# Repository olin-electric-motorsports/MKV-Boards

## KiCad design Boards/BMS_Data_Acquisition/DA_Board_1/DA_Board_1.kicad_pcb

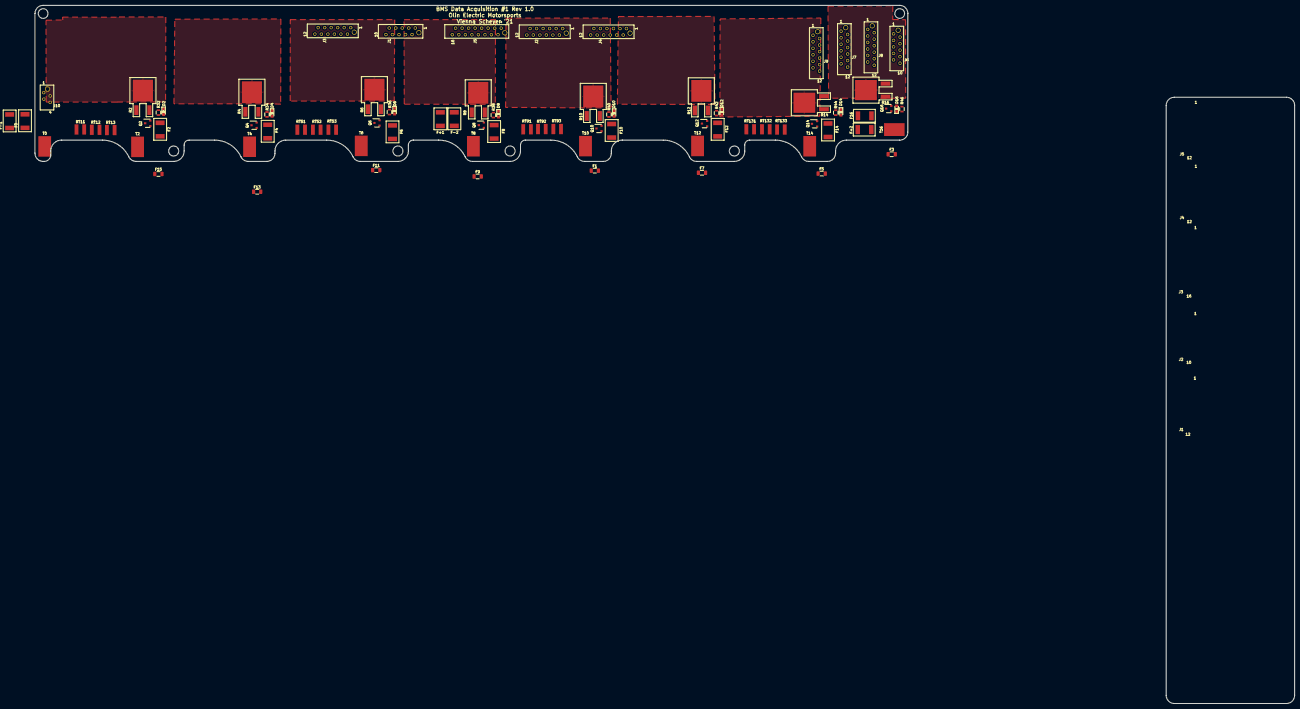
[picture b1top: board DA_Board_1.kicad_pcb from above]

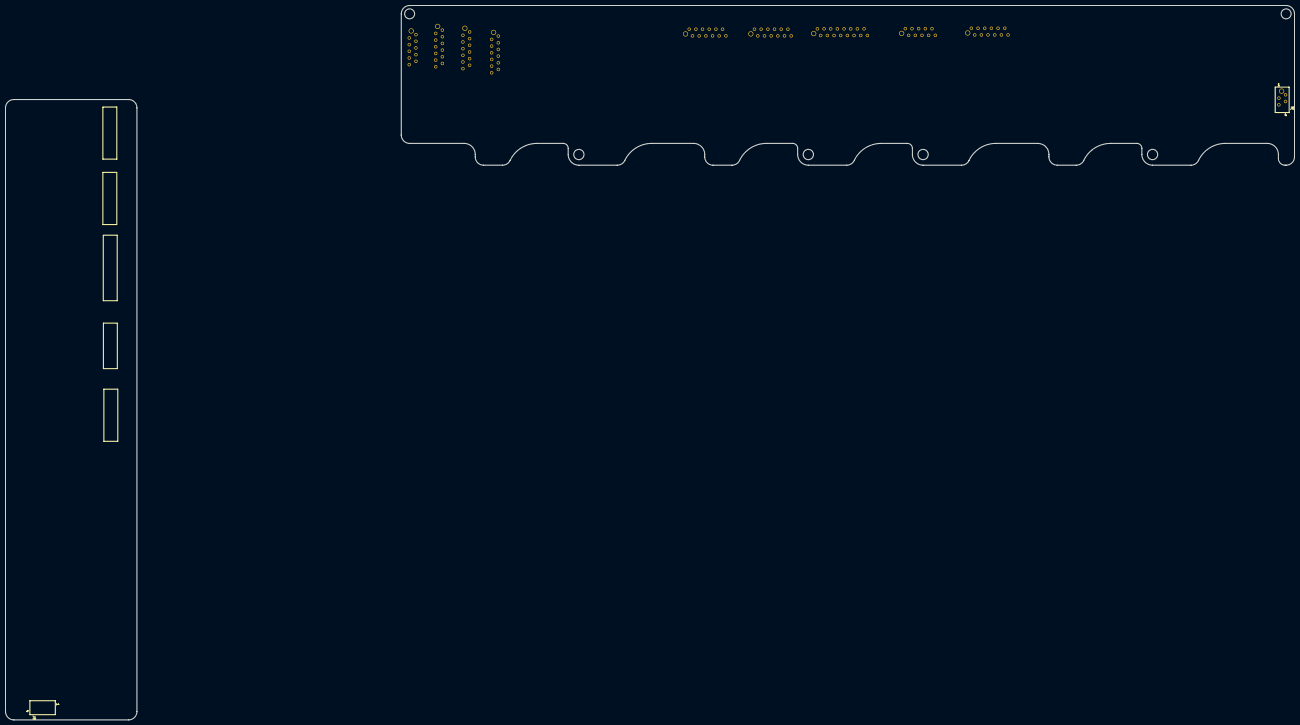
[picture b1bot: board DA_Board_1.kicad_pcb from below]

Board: 2 copper layers, 340.1 x 60.8 mm, 91 parts (7 on the bottom side), 103 nets, no tracks yet.

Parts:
D2, D4, D6, D8, D10, D12, D14, D16: LED_0805; LED_0805_OEM
F0, F2, F4, F6, F8, F10, F12, F14, F16: 200mA_Fuse; Fuse_1812
F1, F3, F5, F7, F9, F11, F13, F15: 1.5A_Fuse; Fuse_1206
F+1, F+2: 200mA_Fuse; Fuse_1812
F-1, F-2: 200mA_Fuse; Fuse_1812
J1, J4: MM_F_VT_12; micromatch_female_vt_12
J1#2, J6: MM_M_VT_10; micromatch_female_vert_10
J2: MM_F_VT_10; micromatch_female_vert_10
J2#2, J3#2, J4#2, J7, J8#3, J9: MM_M_VT_12; micromatch_female_vert_12
J3: MM_F_VT_16; micromatch_female_vert_16
J5: MM_M_VT_12; micromatch_female_vt_12
J5#2: MM_M_VT_16; micromatch_female_vert_16
J8, J8#2, J10: MM_F_VT_04; micromatch_female_vert_4
Q2, Q4, Q6, Q8, Q10, Q12, Q14, Q16: BSS308PE; SOT-23-3_OEM
R2, R4, R6, R8, R10, R12, R14, R16: R_3.3_25W_TO163; PWR163
R32, R34, R36, R38, R40, R42, R44, R46: R_475; R_0805_OEM
RT11, RT12, RT13, RT51, RT52, RT53, RT91, RT92, RT93, RT131, RT132, RT133: Thermistor
T0, T2, T4, T6, T8, T10, T12, T14, T16: Tab_Connect_BMS; Tab_connect_BMS

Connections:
/C0: F0.2, J1#2.9
/C1: J1#2.8, J9.1
/C1_T1: J1#2.7, RT11.1
/C1_T2: J1#2.6, RT12.1
/C1_T3: J1#2.5, RT13.1
/C2: F2.2, J2#2.11
/C3: J1#2.4, J9.8
/C3_T1: J2#2.9, J9.7
/C3_T2: J2#2.8, J9.6
/C3_T3: J2#2.7, J9.5
/C4: F4.2, J2#2.10
/C5: J1#2.3, J9.12
/C5_T1: J1#2.2, RT51.1
/C5_T2: J1#2.1, RT52.1
/C5_T3: J3#2.12, RT53.1
/C6: F6.2, J2#2.6
/C7: J3#2.11, J7.8
/C7_T1: J2#2.2, J7.7
/C7_T2: J2#2.1, J7.6
/C7_T3: J4#2.12, J7.5
/C8: F8.2, J2#2.3
/C9: J3#2.10, J7.12
/C9_T1: J3#2.9, RT91.1
/C9_T2: J3#2.8, RT92.1
/C9_T3: J3#2.7, RT93.1
/C10: F10.2, J4#2.11
/C11: J3#2.6, J8#3.7
/C11_T1: J4#2.9, J8#3.6
/C11_T2: J4#2.8, J8#3.5
/C11_T3: J4#2.7, J8#3.4
/C12: F12.2, J4#2.10
/C13: J3#2.5, J8#3.11
/C13_T1: J3#2.4, RT131.1
/C13_T2: J3#2.3, RT132.1
/C13_T3: J3#2.2, RT133.1
/C14: F14.2, J4#2.6
/C15: J3#2.1, J6.8
/C15_T1: J4#2.3, J6.5
/C15_T2: J4#2.2, J6.4
/C15_T3: J4#2.1, J6.3
/C16: F16.2, J4#2.4
/GND1: J2#2.12, J6.6, RT11.2, RT12.2, RT13.2, RT51.2, RT52.2, RT53.2, RT91.2, RT92.2, RT93.2, RT131.2, RT132.2, RT133.2
/PWR1: F0.1, F-1.1, J9.2, T0.1
/PWR2: J9.4, R2.2, R32.2
/PWR3: F2.1, F15.1, J9.9, T2.1
/PWR4: J9.11, R4.2, R34.2
/PWR5: F4.1, F13.1, J7.2, T4.1
/PWR6: J7.4, R6.2, R36.2
/PWR7: F6.1, F11.1, J7.9, T6.1
/PWR8: J7.11, R8.2, R38.2
/PWR9: F8.1, F9.1, F+1.1, F-2.1, J8#3.1, T8.1
/PWR10: J8#3.3, R10.2, R40.2
/PWR11: F1.1, F10.1, J8#3.8, T10.1
/PWR12: J8#3.10, R12.2, R42.2
/PWR13: F7.1, F12.1, J8#3.12, T12.1
/PWR14: J6.2, R14.2, R44.2
/PWR15: F5.1, F14.1, J6.10, T14.1
/PWR16: J6.7, R16.2, R46.2
/Q1: J5#2.16, J9.3
/Q2: J5#2.15, Q2.1
/Q3: J5#2.14, J9.10
/Q4: J5#2.13, Q4.1
/Q5: J5#2.12, J7.3
/Q6: J5#2.11, Q6.1
/Q7: J5#2.10, J7.10
/Q8: J5#2.9, Q8.1
/Q9: J5#2.8, J8#3.2
/Q10: J5#2.7, Q10.1
/Q11: J5#2.6, J8#3.9
/Q12: J5#2.5, Q12.1
/Q13: J5#2.4, J6.1
/Q14: J5#2.3, Q14.1
/Q15: J5#2.2, J6.9
/Q16: J5#2.1, Q16.1
/V+1: F+1.2, J4#2.5
/V+2: F+2.2, J2#2.5
/V-1: F-1.2, J2#2.4
/V-2: F-2.2, J1#2.10
unnamed: D2.1, R32.1
unnamed: D2.2, Q2.3, R2.1
unnamed: D4.1, R34.1
unnamed: D4.2, Q4.3, R4.1
unnamed: D6.1, R36.1
unnamed: D6.2, Q6.3, R6.1
unnamed: D8.1, R38.1
unnamed: D8.2, Q8.3, R8.1
unnamed: D10.1, R40.1
unnamed: D10.2, Q10.3, R10.1
unnamed: D12.1, R42.1
unnamed: D12.2, Q12.3, R12.1
unnamed: D14.1, R44.1
unnamed: D14.2, Q14.3, R14.1
unnamed: D16.1, R46.1
unnamed: D16.2, Q16.3, R16.1
unnamed: F1.2, Q10.2
unnamed: F3.2, Q16.2
unnamed: F5.2, Q14.2
unnamed: F7.2, Q12.2
unnamed: F9.2, Q8.2
unnamed: F11.2, Q6.2
unnamed: F13.2, Q4.2
unnamed: F15.2, Q2.2
unnamed: F3.1, F16.1, F+2.1, T16.1

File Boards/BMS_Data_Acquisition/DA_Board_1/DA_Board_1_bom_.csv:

Component,Description,Part,References,Value,Footprint,Quantity Per PCB,Datasheet,MPN,MFN,PurchasingLink
1,"LED, Green, 2.2V, 20mA, 0805",LED_0805,D2 D4 D6 D8 D10 D12 D14 D16,LED_0805,LED_0805_OEM,8,http://www.osram-os.com/Graphics/XPic9/00078860_0.pdf,475-1410-1-ND,DK,https://www.digikey.com/products/en?keywords=475-1410-1-ND
2,200mA Fuse,200mA_Fuse,F0 F2 F4 F6 F8 F10 F12 F14 F16 F+1 F+2 F-1 F-2,200mA_Fuse,Fuse_1812,13,https://www.belfuse.com/resources/CircuitProtection/datashee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,,,
3,Micro-MaTch connector 10 pin male vertical,MM_M_VT_10,J1 J6,MM_M_VT_10,micromatch_female_vert_10,2,http://www.te.com/commerce/DocumentDelivery/DDEController?Ac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,1-215464-0,TE,http://www.te.com/global-en/product-1-215464-0.html
4,Micro-MaTch connector 12 pin male vertical,MM_M_VT_12,J2 J3 J4 J7 J8 J9,MM_M_VT_12,micromatch_female_vert_12,6,http://www.te.com/commerce/DocumentDelivery/DDEController?Ac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,1-215464-2,TE,http://www.te.com/global-en/product-1-215464-2.html
5,Micro-MaTch connector 16 pin male vertical,MM_M_VT_16,J5,MM_M_VT_16,micromatch_female_vert_16,1,http://www.te.com/commerce/DocumentDelivery/DDEController?Ac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,1-215464-6,TE,http://www.te.com/global-en/product-1-215464-6.html
6,"MOSFET, P-channel, 30V, 2A",BSS308PE,Q2 Q4 Q6 Q8 Q10 Q12 Q14 Q16,BSS308PE,SOT-23-3_OEM,8,https://www.infineon.com/dgdl/BSS308PE_Rev2.03.pdf?folderId=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,BSS308PEH6327XTSA1CT-ND,DK,https://www.digikey.com/products/en/discrete-semiconductor-p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
7,RES SMD 3.3 OHM 1% 25W DPAK,R_3.3_25W_TO163,R2 R4 R6 R8 R10 R12 R14 R16,R_3.3_25W_TO163,PWR163,8,https://www.bourns.com/docs/Product-Datasheets/PWR163.pdf,PWR163S-25-3R30F-ND,DK,https://www.digikey.com/products/en?keywords=PWR163S-25-3R30F-ND
8,"Resistor, 475, 0.125W, 1%, 0805",R_475,R32 R34 R36 R38 R40 R42 R44 R46,R_475,R_0805_OEM,8,http://www.yageo.com.tw/exep/pages/download/literatures/PYu-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,311-475CRCT-ND,DK,https://www.digikey.com/products/en?keywords=311-475CRCT-ND
9,,Thermistor,RT11 RT12 RT13 RT51 RT52 RT53 RT91 RT92 RT93 RT131 RT132 RT133,Thermistor,Thermistor,12,,,,
10,,Tab_Connect_BMS,T0 T2 T4 T6 T8 T10 T12 T14 T16,Tab_Connect_BMS,Tab_connect_BMS,9,,,,
,,,,,,,,,,
,,,,,,,,,,
,,,,,,,,,,
,,,,,,,,,,
,,,,,,,,,,
Component Groups:,10,,,,,,,,,
Component Count:,75,,,,,,,,,
Fitted Components:,75,,,,,,,,,
Number of PCBs:,1,,,,,,,,,
Total components:,75,,,,,,,,,
Schematic Version:,,,,,,,,,,
Schematic Date:,2019-09-18,,,,,,,,,
PCB Variant:,[u'default'],,,,,,,,,
BoM Date:,Mon 11 Nov 2019 08:43:34 PM EST,,,,,,,,,
Schematic Source:,/home/vscheyer/Desktop/Formula/MKV-Boards/Boards/BMS_Data_Acquisition/DA_Board_1/DA_Board_1.sch,,,,,,,,,
KiCad Version:,Eeschema 5.0.2-bee76a0~70~ubuntu16.04.1,,,,,,,,,

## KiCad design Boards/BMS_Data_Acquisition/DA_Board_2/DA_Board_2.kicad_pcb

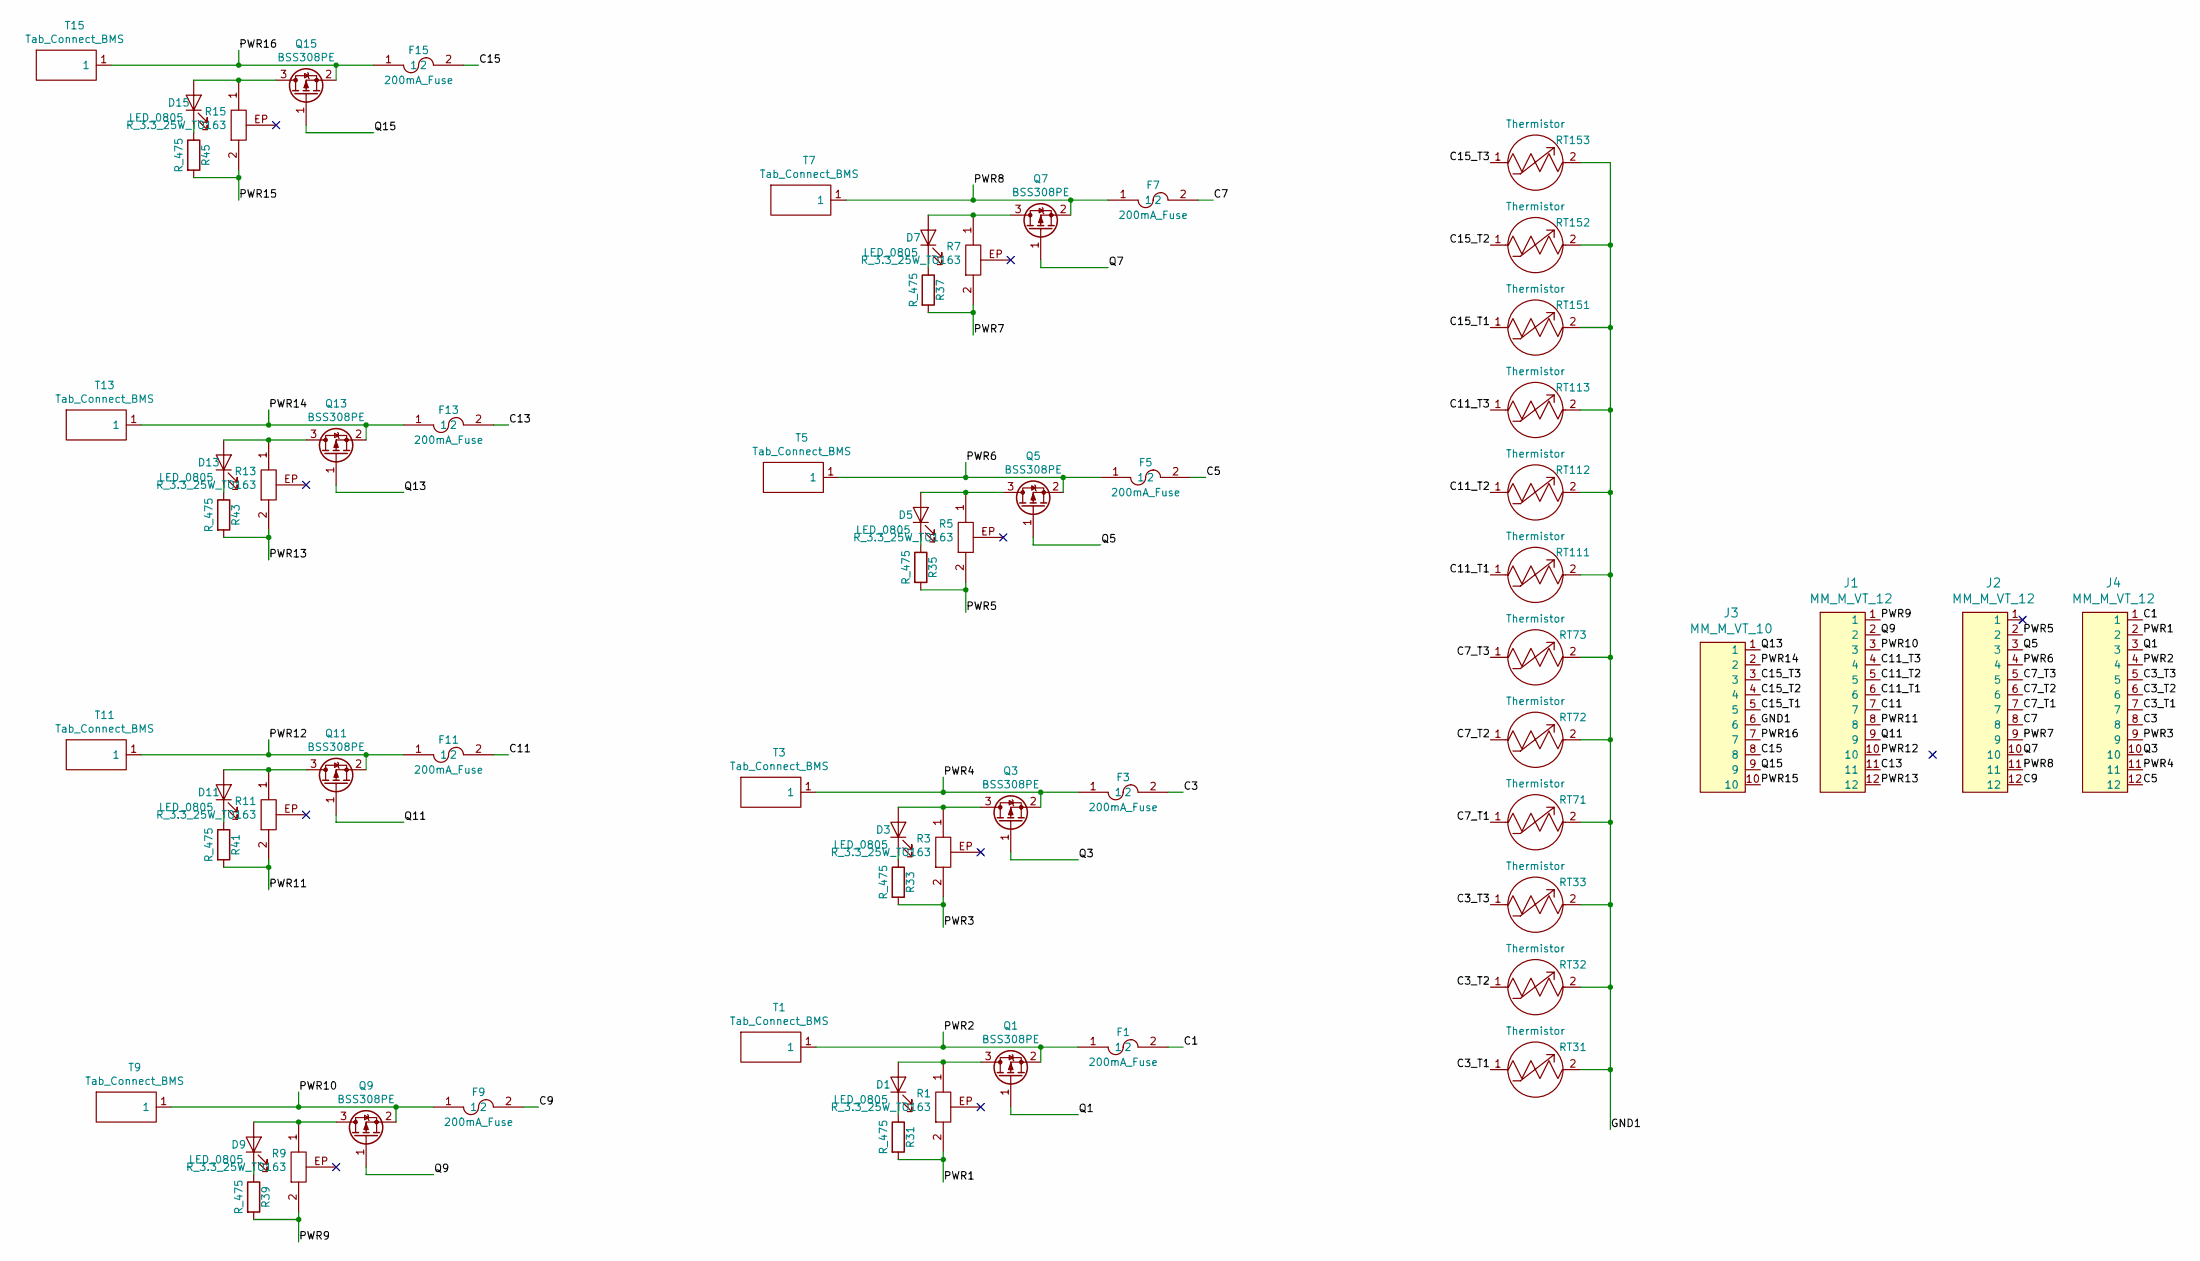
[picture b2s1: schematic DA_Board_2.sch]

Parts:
D1, D3, D5, D7, D9, D11, D13, D15: LED_0805; LED_0805_OEM; MPN 475-1410-1-ND
F1, F3, F5, F7, F9, F11, F13, F15: 200mA_Fuse; Fuse_1812
J1, J2, J4: MM_M_VT_12; micromatch_female_vert_12; MPN 1-215464-2
J3: MM_M_VT_10; micromatch_female_vert_10; MPN 1-215464-0
Q1, Q3, Q5, Q7, Q9, Q11, Q13, Q15: BSS308PE; SOT-23-3_OEM; MPN BSS308PEH6327XTSA1CT-ND
R1, R3, R5, R7, R9, R11, R13, R15: R_3.3_25W_TO163; PWR163; MPN PWR163S-25-3R30F-ND
R31, R33, R35, R37, R39, R41, R43, R45: R_475; R_0805_OEM; MPN 311-475CRCT-ND
RT31, RT32, RT33, RT71, RT72, RT73, RT111, RT112, RT113, RT151, RT152, RT153: Thermistor
T1, T3, T5, T7, T9, T11, T13, T15: Tab_Connect_BMS; Tab_connect_BMS

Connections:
/C1: F1.2, J4.1
/C3: F3.2, J4.8
/C3_T1: J4.7, RT31.1
/C3_T2: J4.6, RT32.1
/C3_T3: J4.5, RT33.1
/C5: F5.2, J4.12
/C7: F7.2, J2.8
/C7_T1: J2.7, RT71.1
/C7_T2: J2.6, RT72.1
/C7_T3: J2.5, RT73.1
/C9: F9.2, J2.12
/C11: F11.2, J1.7
/C11_T1: J1.6, RT111.1
/C11_T2: J1.5, RT112.1
/C11_T3: J1.4, RT113.1
/C13: F13.2, J1.11
/C15: F15.2, J3.8
/C15_T1: J3.5, RT151.1
/C15_T2: J3.4, RT152.1
/C15_T3: J3.3, RT153.1
/GND1: J3.6, RT31.2, RT32.2, RT33.2, RT71.2, RT72.2, RT73.2, RT111.2, RT112.2, RT113.2, RT151.2, RT152.2, RT153.2
/PWR1: J4.2, R1.2, R31.2
/PWR2: F1.1, J4.4, Q1.2 (S), T1.1
/PWR3: J4.9, R3.2, R33.2
/PWR4: F3.1, J4.11, Q3.2 (S), T3.1
/PWR5: J2.2, R5.2, R35.2
/PWR6: F5.1, J2.4, Q5.2 (S), T5.1
/PWR7: J2.9, R7.2, R37.2
/PWR8: F7.1, J2.11, Q7.2 (S), T7.1
/PWR9: J1.1, R9.2, R39.2
/PWR10: F9.1, J1.3, Q9.2 (S), T9.1
/PWR11: J1.8, R11.2, R41.2
/PWR12: F11.1, J1.10, Q11.2 (S), T11.1
/PWR13: J1.12, R13.2, R43.2
/PWR14: F13.1, J3.2, Q13.2 (S), T13.1
/PWR15: J3.10, R15.2, R45.2
/PWR16: F15.1, J3.7, Q15.2 (S), T15.1
/Q1: J4.3, Q1.1 (G)
/Q3: J4.10, Q3.1 (G)
/Q5: J2.3, Q5.1 (G)
/Q7: J2.10, Q7.1 (G)
/Q9: J1.2, Q9.1 (G)
/Q11: J1.9, Q11.1 (G)
/Q13: J3.1, Q13.1 (G)
/Q15: J3.9, Q15.1 (G)
unnamed: D1.1 (K), R31.1
unnamed: D1.2 (A), Q1.3 (D), R1.1
unnamed: D3.1 (K), R33.1
unnamed: D3.2 (A), Q3.3 (D), R3.1
unnamed: D5.1 (K), R35.1
unnamed: D5.2 (A), Q5.3 (D), R5.1
unnamed: D7.1 (K), R37.1
unnamed: D7.2 (A), Q7.3 (D), R7.1
unnamed: D9.1 (K), R39.1
unnamed: D9.2 (A), Q9.3 (D), R9.1
unnamed: D11.1 (K), R41.1
unnamed: D11.2 (A), Q11.3 (D), R11.1
unnamed: D13.1 (K), R43.1
unnamed: D13.2 (A), Q13.3 (D), R13.1
unnamed: D15.1 (K), R45.1
unnamed: D15.2 (A), Q15.3 (D), R15.1

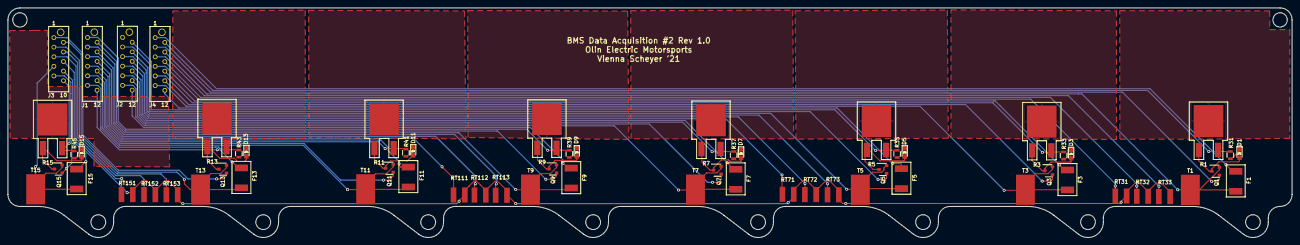
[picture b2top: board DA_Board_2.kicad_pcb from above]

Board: 2 copper layers, 340.1 x 60.8 mm, 64 parts (0 on the bottom side), 61 nets.

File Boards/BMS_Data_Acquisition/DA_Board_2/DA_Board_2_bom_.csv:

Component,Description,Part,References,Value,Footprint,Quantity Per PCB,Datasheet,MPN,MFN,PurchasingLink
1,"LED, Green, 2.2V, 20mA, 0805",LED_0805,D1 D3 D5 D7 D9 D11 D13 D15,LED_0805,LED_0805_OEM,8,http://www.osram-os.com/Graphics/XPic9/00078860_0.pdf,475-1410-1-ND,DK,https://www.digikey.com/products/en?keywords=475-1410-1-ND
2,200mA Fuse,200mA_Fuse,F1 F3 F5 F7 F9 F11 F13 F15,200mA_Fuse,Fuse_1812,8,https://www.belfuse.com/resources/CircuitProtection/datashee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,,,
3,Micro-MaTch connector 10 pin male vertical,MM_M_VT_10,J3,MM_M_VT_10,micromatch_female_vert_10,1,http://www.te.com/commerce/DocumentDelivery/DDEController?Ac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,1-215464-0,TE,http://www.te.com/global-en/product-1-215464-0.html
4,Micro-MaTch connector 12 pin male vertical,MM_M_VT_12,J1 J2 J4,MM_M_VT_12,micromatch_female_vert_12,3,http://www.te.com/commerce/DocumentDelivery/DDEController?Ac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,1-215464-2,TE,http://www.te.com/global-en/product-1-215464-2.html
5,"MOSFET, P-channel, 30V, 2A",BSS308PE,Q1 Q3 Q5 Q7 Q9 Q11 Q13 Q15,BSS308PE,SOT-23-3_OEM,8,https://www.infineon.com/dgdl/BSS308PE_Rev2.03.pdf?folderId=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,BSS308PEH6327XTSA1CT-ND,DK,https://www.digikey.com/products/en/discrete-semiconductor-p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
6,RES SMD 3.3 OHM 1% 25W DPAK,R_3.3_25W_TO163,R1 R3 R5 R7 R9 R11 R13 R15,R_3.3_25W_TO163,PWR163,8,https://www.bourns.com/docs/Product-Datasheets/PWR163.pdf,PWR163S-25-3R30F-ND,DK,https://www.digikey.com/products/en?keywords=PWR163S-25-3R30F-ND
7,"Resistor, 475, 0.125W, 1%, 0805",R_475,R31 R33 R35 R37 R39 R41 R43 R45,R_475,R_0805_OEM,8,http://www.yageo.com.tw/exep/pages/download/literatures/PYu-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,311-475CRCT-ND,DK,https://www.digikey.com/products/en?keywords=311-475CRCT-ND
8,,Thermistor,RT31 RT32 RT33 RT71 RT72 RT73 RT111 RT112 RT113 RT151 RT152 RT153,Thermistor,Thermistor,12,,,,
9,,Tab_Connect_BMS,T1 T3 T5 T7 T9 T11 T13 T15,Tab_Connect_BMS,Tab_connect_BMS,8,,,,
,,,,,,,,,,
,,,,,,,,,,
,,,,,,,,,,
,,,,,,,,,,
,,,,,,,,,,
Component Groups:,9,,,,,,,,,
Component Count:,64,,,,,,,,,
Fitted Components:,64,,,,,,,,,
Number of PCBs:,1,,,,,,,,,
Total components:,64,,,,,,,,,
Schematic Version:,,,,,,,,,,
Schematic Date:,,,,,,,,,,
PCB Variant:,default,,,,,,,,,
BoM Date:,Mon 11 Nov 2019 08:40:20 PM EST,,,,,,,,,
Schematic Source:,/home/vscheyer/Desktop/Formula/MKV-Boards/Boards/BMS_Data_Acquisition/DA_Board_2/DA_Board_2.sch,,,,,,,,,
KiCad Version:,Eeschema 5.0.2-bee76a0~70~ubuntu16.04.1,,,,,,,,,

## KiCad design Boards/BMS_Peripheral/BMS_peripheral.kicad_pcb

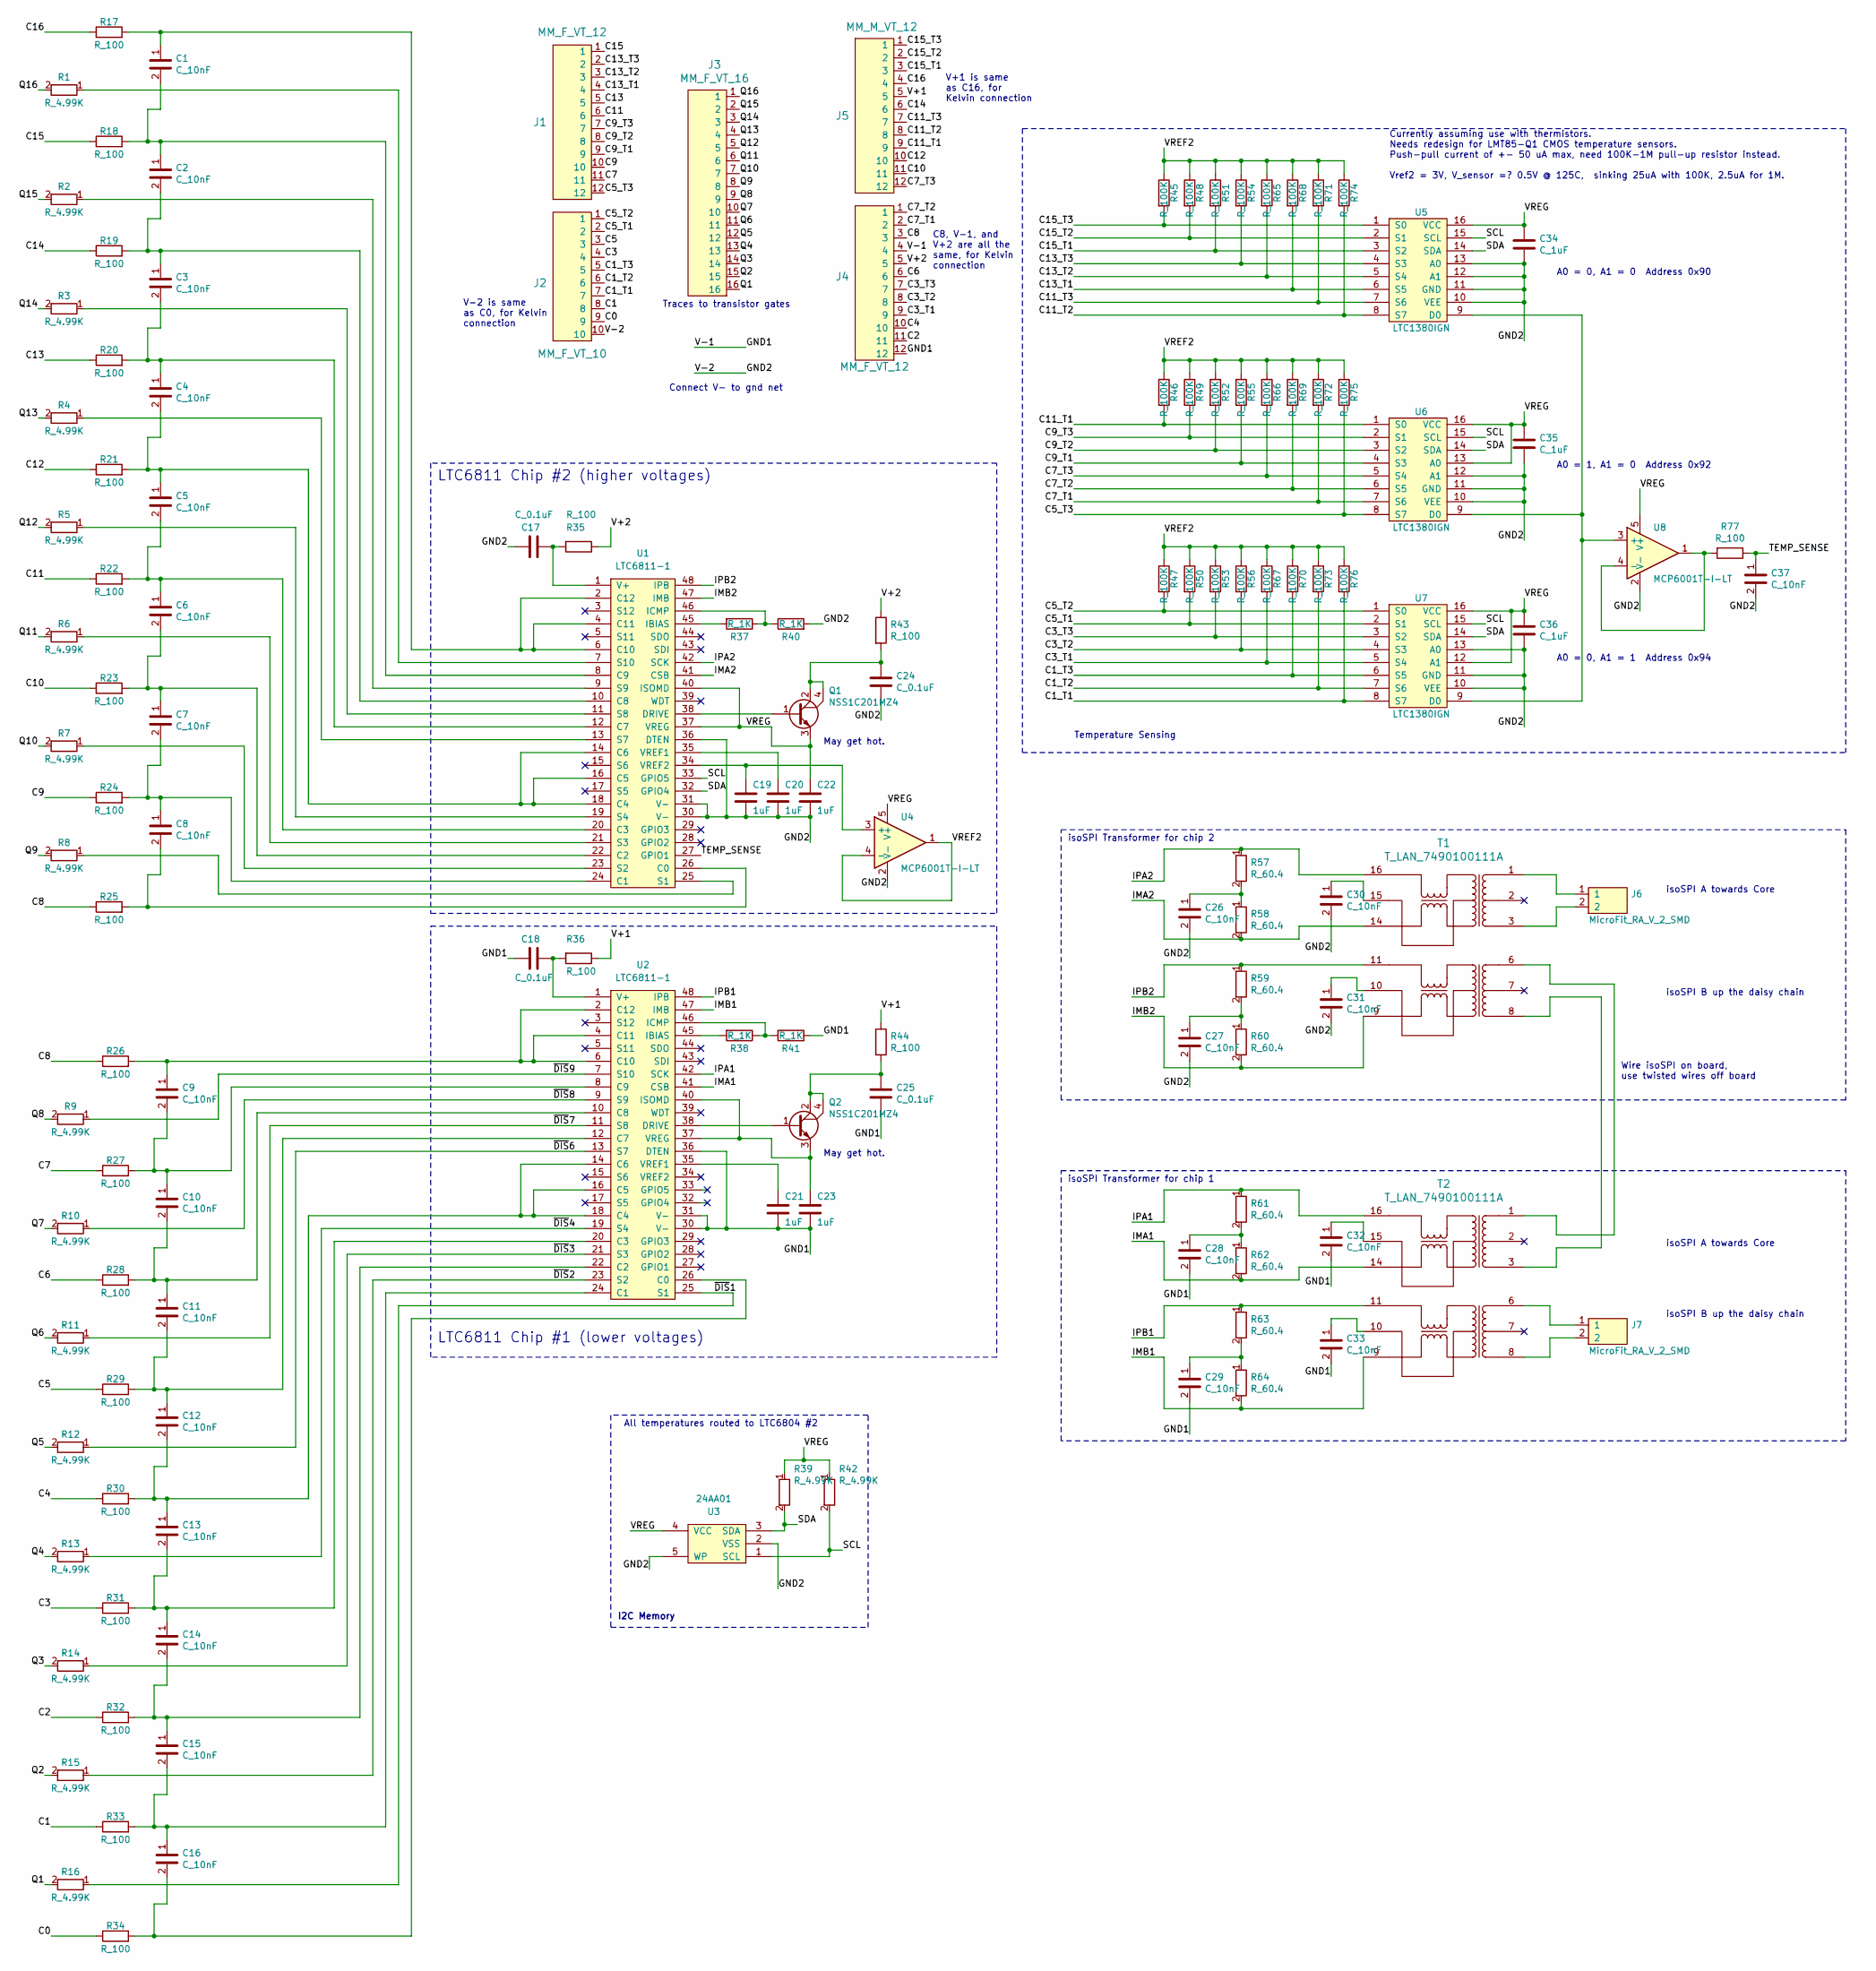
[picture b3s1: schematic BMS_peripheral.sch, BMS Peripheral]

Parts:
C1, C2, C3, C4, C5, C6, C7, C8, C9, C10, C11, C12, C13, C14, C15, C16, C26, C27, C28, C29, C30, C31, C32, C33: C_10nF; C_0805_OEM; MPN 1276-1015-1-ND
C17, C18, C24, C25: C_0.1uF; C_0805_OEM; MPN 478-3352-1-ND
C19, C20, C21, C22, C23: 1uF; C_0805_OEM; MPN 1276-2887-1-ND
C34, C35, C36: C_1uF; C_0805_OEM; MPN 1276-2887-1-ND
C37: C_10nF; C_0805_OEM
J1, J4: MM_F_VT_12; micromatch_female_vt_12; MPN 1-338068-2
J2: MM_F_VT_10; micromatch_female_vert_10; MPN 1-338068-0
J3: MM_F_VT_16; micromatch_female_vert_16; MPN 1-338068-6
J5: MM_M_VT_12; micromatch_female_vt_12; MPN 1-215464-2
J6, J7: MicroFit_RA_V_2_SMD; MicroFit_RA_2_SMD; MPN 436500213
Q1, Q2: NSS1C201MZ4; SOT-223; MPN NSS1C201MZ4T3GOSCT-ND
R1, R2, R3, R4, R5, R6, R7, R8, R9, R10, R11, R12, R13, R14, R15, R16: R_4.99K; R_0805_OEM
R17, R18, R19, R20, R21, R22, R23, R24, R25, R26, R27, R28, R29, R30, R31, R32, R33, R34, R35, R36, R43, R44, R77: R_100; R_0805_OEM; MPN RNCP0805FTD100RCT-ND
R37, R38, R40, R41: R_1K; R_0805_OEM; MPN RNCP0805FTD1K00CT-ND
R39, R42: R_4.99K; R_0805_OEM; MPN RNCP0805FTD4K99CT-ND
R45, R46, R47, R48, R49, R50, R51, R52, R53, R54, R55, R56, R65, R66, R67, R68, R69, R70, R71, R72, R73, R74, R75, R76: R_100K; R_0805_OEM; MPN P100KCCT-ND
R57, R58, R59, R60, R61, R62, R63, R64: R_60.4; R_0805_OEM; MPN P60.4DACT-ND
T1, T2: T_LAN_7490100111A; MPN 732-5711-1-ND
U1, U2: LTC6811-1; TSSOP-48_LTC6811-1; MPN LTC6811IG-1-PBF-ND
U3: 24AA01; SOT-23-5_OEM_24AA01; MPN CAT24AA01TDI-GT3OSCT-ND
U4, U8: MCP6001T-I-LT; SOT-353_SC-70-5; MPN MCP6001T-I/LTCT-ND
U5, U6, U7: LTC1380IGN; SSOP-16_3.9x4.9mm_P0.635mm; MPN LTC1380IGN#PBF-ND

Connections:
/C0: J2.9, R34.1
/C1: J2.8, R33.1
/C1_T1: J2.7, R76.2, U7.8 (S7)
/C1_T2: J2.6, R73.2, U7.7 (S6)
/C1_T3: J2.5, R70.2, U7.6 (S5)
/C2: J4.11, R32.1
/C3: J2.4, R31.1
/C3_T1: J4.9, R67.2, U7.5 (S4)
/C3_T2: J4.8, R56.2, U7.4 (S3)
/C3_T3: J4.7, R53.2, U7.3 (S2)
/C4: J4.10, R30.1
/C5: J2.3, R29.1
/C5_T1: J2.2, R50.2, U7.2 (S1)
/C5_T2: J2.1, R47.2, U7.1 (S0)
/C5_T3: J1.12, R75.2, U6.8 (S7)
/C6: J4.6, R28.1
/C7: J1.11, R27.1
/C7_T1: J4.2, R72.2, U6.7 (S6)
/C7_T2: J4.1, R69.2, U6.6 (S5)
/C7_T3: J5.12, R66.2, U6.5 (S4)
/C8: J4.3, R25.1, R26.1
/C9: J1.10, R24.1
/C9_T1: J1.9, R55.2, U6.4 (S3)
/C9_T2: J1.8, R52.2, U6.3 (S2)
/C9_T3: J1.7, R49.2, U6.2 (S1)
/C10: J5.11, R23.1
/C11: J1.6, R22.1
/C11_T1: J5.9, R46.2, U6.1 (S0)
/C11_T2: J5.8, R74.2, U5.8 (S7)
/C11_T3: J5.7, R71.2, U5.7 (S6)
/C12: J5.10, R21.1
/C13: J1.5, R20.1
/C13_T1: J1.4, R68.2, U5.6 (S5)
/C13_T2: J1.3, R65.2, U5.5 (S4)
/C13_T3: J1.2, R54.2, U5.4 (S3)
/C14: J5.6, R19.1
/C15: J1.1, R18.1
/C15_T1: J5.3, R51.2, U5.3 (S2)
/C15_T2: J5.2, R48.2, U5.2 (S1)
/C15_T3: J5.1, R45.2, U5.1 (S0)
/C16: J5.4, R17.1
/GND1: C18.2, C21.2, C23.2, C25.2, C28.2, C29.2, C32.2, C33.2, J4.4, J4.12, R41.2, U2.30 (V-), U2.31 (V-), U2.36 (DTEN)
/GND2: C17.2, C19.2, C20.2, C22.2, C24.2, C26.2, C27.2, C30.2, C31.2, C34.2, C35.2, C36.2, C37.2, J2.10, R40.2, U1.30 (V-), U1.31 (V-), U1.36 (DTEN), U3.2 (VSS), U3.5 (WP), U4.2 (V-), U5.10 (VEE), U5.11 (GND), U5.12 (A1), U5.13 (A0), U6.10 (VEE), U6.11 (GND), U6.12 (A1), U7.10 (VEE), U7.11 (GND), U7.13 (A0), U8.2 (V-)
/IMA1: R62.2, T2.14, U2.41 (CSB)
/IMA2: R58.2, T1.14, U1.41 (CSB)
/IMB1: R64.2, T2.9, U2.47 (IMB)
/IMB2: R60.2, T1.9, U1.47 (IMB)
/IPA1: R61.1, T2.16, U2.42 (SCK)
/IPA2: R57.1, T1.16, U1.42 (SCK)
/IPB1: R63.1, T2.11, U2.48 (IPB)
/IPB2: R59.1, T1.11, U1.48 (IPB)
/Q1: J3.16, R16.2
/Q2: J3.15, R15.2
/Q3: J3.14, R14.2
/Q4: J3.13, R13.2
/Q5: J3.12, R12.2
/Q6: J3.11, R11.2
/Q7: J3.10, R10.2
/Q8: J3.9, R9.2
/Q9: J3.8, R8.2
/Q10: J3.7, R7.2
/Q11: J3.6, R6.2
/Q12: J3.5, R5.2
/Q13: J3.4, R4.2
/Q14: J3.3, R3.2
/Q15: J3.2, R2.2
/Q16: J3.1, R1.2
/SCL: R42.2, U1.33 (GPIO5), U3.1 (SCL), U5.15 (SCL), U6.15 (SCL), U7.15 (SCL)
/SDA: R39.2, U1.32 (GPIO4), U3.3 (SDA), U5.14 (SDA), U6.14 (SDA), U7.14 (SDA)
/TEMP_SENSE: C37.1, R77.1, U1.27 (GPIO1)
/V+1: J5.5, R36.1, R44.1
/V+2: J4.5, R35.1, R43.1
/VREF2: R45.1, R46.1, R47.1, R48.1, R49.1, R50.1, R51.1, R52.1, R53.1, R54.1, R55.1, R56.1, R65.1, R66.1, R67.1, R68.1, R69.1, R70.1, R71.1, R72.1, R73.1, R74.1, R75.1, R76.1, U4.1, U4.4 (-)
/VREG: C22.1, C34.1, C35.1, C36.1, Q1.3, R39.1, R42.1, U1.37 (VREG), U1.40 (ISOMD), U3.4 (VCC), U4.5 (V+), U5.16 (VCC), U6.13 (A0), U6.16 (VCC), U7.12 (A1), U7.16 (VCC), U8.5 (V+)
/~DIS~1: R16.1, U2.25 (S1)
/~DIS~2: R15.1, U2.23 (S2)
/~DIS~3: R14.1, U2.21 (S3)
/~DIS~4: R13.1, U2.19 (S4)
/~DIS~6: R12.1, U2.13 (S7)
/~DIS~7: R11.1, U2.11 (S8)
/~DIS~8: R10.1, U2.9 (S9)
/~DIS~9: R9.1, U2.7 (S10)
unnamed: C1.1, R17.2, U1.2 (C12), U1.4 (C11), U1.6 (C10)
unnamed: C1.2, C2.1, R18.2, U1.8 (C9)
unnamed: C2.2, C3.1, R19.2, U1.10 (C8)
unnamed: C3.2, C4.1, R20.2, U1.12 (C7)
unnamed: C4.2, C5.1, R21.2, U1.14 (C6), U1.16 (C5), U1.18 (C4)
unnamed: C5.2, C6.1, R22.2, U1.20 (C3)
unnamed: C6.2, C7.1, R23.2, U1.22 (C2)
unnamed: C7.2, C8.1, R24.2, U1.24 (C1)
unnamed: C8.2, R25.2, U1.26 (C0)
unnamed: C9.1, R26.2, U2.2 (C12), U2.4 (C11), U2.6 (C10)
unnamed: C9.2, C10.1, R27.2, U2.8 (C9)
unnamed: C10.2, C11.1, R28.2, U2.10 (C8)
unnamed: C11.2, C12.1, R29.2, U2.12 (C7)
unnamed: C12.2, C13.1, R30.2, U2.14 (C6), U2.16 (C5), U2.18 (C4)
unnamed: C13.2, C14.1, R31.2, U2.20 (C3)
unnamed: C14.2, C15.1, R32.2, U2.22 (C2)
unnamed: C15.2, C16.1, R33.2, U2.24 (C1)
unnamed: C16.2, R34.2, U2.26 (C0)
unnamed: C17.1, R35.2, U1.1 (V+)
unnamed: C18.1, R36.2, U2.1 (V+)
unnamed: C19.1, U1.34 (VREF2), U4.3 (+)
unnamed: C20.1, U1.35 (VREF1)
unnamed: C21.1, U2.35 (VREF1)
unnamed: C23.1, Q2.3, U2.37 (VREG), U2.40 (ISOMD)
unnamed: C24.1, Q1.2, Q1.4, R43.2
unnamed: C25.1, Q2.2, Q2.4, R44.2
unnamed: C26.1, R57.2, R58.1
unnamed: C27.1, R59.2, R60.1
unnamed: C28.1, R61.2, R62.1
unnamed: C29.1, R63.2, R64.1
unnamed: C30.1, T1.15
unnamed: C31.1, T1.10
unnamed: C32.1, T2.15
unnamed: C33.1, T2.10
unnamed: J6.1, T1.1
unnamed: J6.2, T1.3
unnamed: J7.1, T2.6
unnamed: J7.2, T2.8
unnamed: Q1.1, U1.38 (DRIVE)
unnamed: Q2.1, U2.38 (DRIVE)
unnamed: R1.1, U1.7 (S10)
unnamed: R2.1, U1.9 (S9)
unnamed: R3.1, U1.11 (S8)
unnamed: R4.1, U1.13 (S7)
unnamed: R5.1, U1.19 (S4)
unnamed: R6.1, U1.21 (S3)
unnamed: R7.1, U1.23 (S2)
unnamed: R8.1, U1.25 (S1)
unnamed: R37.1, R40.1, U1.46 (ICMP)
unnamed: R37.2, U1.45 (IBIAS)
unnamed: R38.1, R41.1, U2.46 (ICMP)
unnamed: R38.2, U2.45 (IBIAS)
unnamed: R77.2, U8.1, U8.4 (-)
unnamed: T1.6, T2.1
unnamed: T1.8, T2.3
unnamed: U5.9 (D0), U6.9 (D0), U7.9 (D0), U8.3 (+)

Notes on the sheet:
I2C Memory
A0 = 0, A1 = 0 Address 0x90
A0 = 1, A1 = 0 Address 0x92
A0 = 0, A1 = 1 Address 0x94
Temperature Sensing
Currently assuming use with thermistors. Needs redesign for LMT85-Q1 CMOS temperature sensors. Push-pull current of +- 50 uA max, need 100K-1M pull-up resistor instead. Vref2 = 3V, V_sensor =? 0.5V @ 125C, sinking 25uA with 100K, 2.5uA for 1M.
May get hot.
isoSPI A towards Core
isoSPI B up the daisy chain
isoSPI Transformer for chip 2
Connect V- to gnd net
isoSPI Transformer for chip 1
All temperatures routed to LTC6804 #2
Wire isoSPI on board, use twisted wires off board
V-2 is same as C0, for Kelvin connection
C8, V-1, and V+2 are all the same, for Kelvin connection
V+1 is same as C16, for Kelvin connection
Traces to transistor gates
LTC6811 Chip #2 (higher voltages)
LTC6811 Chip #1 (lower voltages)

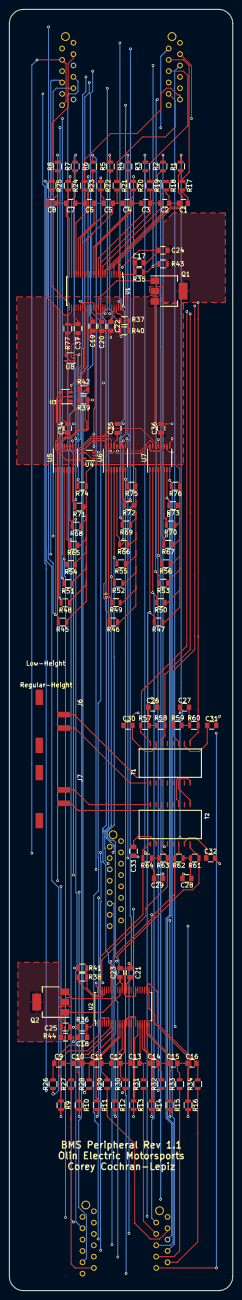
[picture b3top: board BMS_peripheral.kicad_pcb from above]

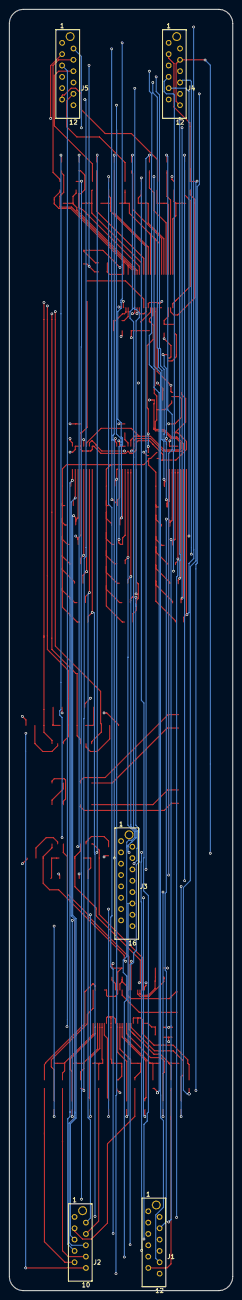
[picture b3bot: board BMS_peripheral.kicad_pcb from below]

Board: 4 copper layers, 50.0 x 287.0 mm, 133 parts (5 on the bottom side), 138 nets.
